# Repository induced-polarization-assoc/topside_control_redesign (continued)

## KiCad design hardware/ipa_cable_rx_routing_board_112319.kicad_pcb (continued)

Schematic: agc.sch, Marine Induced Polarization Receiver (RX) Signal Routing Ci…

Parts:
C901, C902, C911, C912, C921, C922, C931, C932: 10uF; CP_Elec_4x5.4
C903, C904, C907, C908, C925, C926, C929, C930: 0.1uF; C_0805_2012Metric
C905, C906, C927, C928: 10pF; C_0805_2012Metric
C909, C910, C923, C924: 0.33uF; C_0805_2012Metric
C913, C914, C919, C920: 2.2uF; C_0805_2012Metric
C915, C916, C917, C918: 0.022uF; C_0805_2012Metric
IC901, IC902, IC903, IC904: ADP3339AKCZ-1.5-R7; SOT-223-3_TabPin2
R901, R904, R929, R932: 1M; R_0805_2012Metric
R902, R903, R907, R908, R911, R912, R913, R914, R919, R920, R921, R922, R925, R926, R930, R931: 1K; R_0805_2012Metric
R905, R906, R927, R928: 100K; R_0805_2012Metric
R909, R910, R923, R924: 9.09K; R_0805_2012Metric
R915, R916, R917, R918: 10K; R_0805_2012Metric
RV901, RV902, RV903, RV904: 100K; Potentiometer_Vishay_TS53YJ_Vertical
U901, U904, U906, U909: AD8336ACPZ-R7; LFCSP-16-1EP_3x3mm_P0.5mm_EP1.6x1.6mm_ThermalVias
U902, U903, U907, U908: AD736ARZ; SOIC-8_3.9x4.9mm_P1.27mm
U905: AD8554ARZ-REEL7; SOIC-14_3.9x8.7mm_P1.27mm

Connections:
+5VA: C907.1, C908.1, C925.1, C926.1, IC901.3 (IN), IC902.3 (IN), IC903.3 (IN), IC904.3 (IN), U901.13 (VPOS), U902.7 (+VS), U903.7 (+VS), U904.13 (VPOS), U905.4 (V+), U906.13 (VPOS), U907.7 (+VS), U908.7 (+VS), U909.13 (VPOS); also elsewhere on the board
-5VA: C909.2, C910.2, C923.2, C924.2, U901.10 (VNEG), U902.4 (-VS), U903.4 (-VS), U904.10 (VNEG), U906.10 (VNEG), U907.4 (-VS), U908.4 (-VS), U909.10 (VNEG); also elsewhere on the board
/RA: R902.2; also elsewhere on the board
/RB: R930.2; also elsewhere on the board
/RC: R903.2; also elsewhere on the board
/RD: R931.2; also elsewhere on the board
/auto_gain_control/AGC_1_OUT: C901.2; also elsewhere on the board
/auto_gain_control/AGC_2_OUT: C931.2; also elsewhere on the board
/auto_gain_control/AGC_3_OUT: C902.2; also elsewhere on the board
/auto_gain_control/AGC_4_OUT: C932.2; also elsewhere on the board
/auto_gain_control/agc_1/AGC_A_FEEDBACK: C915.2, R915.1, U902.6 (OUTPUT), U905.6 (-INB)
/auto_gain_control/agc_1/AGC_A_GPOS: C913.1, C915.1, U901.11 (GPOS), U905.7 (OUTB)
/auto_gain_control/agc_1/AGC_A_TRIM: RV901.2, U905.5 (+INB)
/auto_gain_control/agc_1/AGC_B_FEEDBACK: C917.2, R917.1, U905.2 (-INA), U907.6 (OUTPUT)
/auto_gain_control/agc_1/AGC_B_GPOS: C917.1, C919.1, U905.1 (OUTA), U906.11 (GPOS)
/auto_gain_control/agc_1/AGC_B_TRIM: RV903.2, U905.3 (+INA)
/auto_gain_control/agc_1/AGC_C_FEEDBACK: C916.2, R916.1, U903.6 (OUTPUT), U905.9 (-INC)
/auto_gain_control/agc_1/AGC_C_GPOS: C914.1, C916.1, U904.11 (GPOS), U905.8 (OUTC)
/auto_gain_control/agc_1/AGC_C_TRIM: RV902.2, U905.10 (+INC)
/auto_gain_control/agc_1/AGC_D_FEEDBACK: C918.2, R918.1, U905.13 (-IND), U908.6 (OUTPUT)
/auto_gain_control/agc_1/AGC_D_GPOS: C918.1, C920.1, U905.14 (OUTD), U909.11 (GPOS)
/auto_gain_control/agc_1/AGC_D_TRIM: RV904.2, U905.12 (+IND)
/auto_gain_control/agc_1/GNEG: R911.1, R912.1, R913.2, R914.2, R919.2, R920.2, R921.1, R922.1, U901.12 (GNEG), U904.12 (GNEG), U906.12 (GNEG), U909.12 (GNEG)
GNDA: C907.2, C908.2, C911.2, C912.2, C921.2, C922.2, C925.2, C926.2, R901.1, R904.1, R913.1, R914.1, R919.1, R920.1, R929.1, R932.1, RV901.3, RV902.3, RV903.3, RV904.3, U901.2 (PWRA), U901.3 (VCOM), U901.4 (INPP), U901.17 (EPAD), U902.1 (CC), U902.8 (COM), U903.1 (CC), U903.8 (COM), U904.2 (PWRA), U904.3 (VCOM), U904.4 (INPP), U904.17 (EPAD), U905.11 (V-), U906.2 (PWRA), U906.3 (VCOM), U906.4 (INPP), U906.17 (EPAD), U907.1 (CC), U907.8 (COM), U908.1 (CC), U908.8 (COM), U909.2 (PWRA), U909.3 (VCOM), U909.4 (INPP), U909.17 (EPAD); also elsewhere on the board
unnamed: C901.1, C903.1, R905.2
unnamed: C902.1, C904.1, R906.2
unnamed: C903.2, R904.2, U902.2 (VIN)
unnamed: C904.2, R901.2, U903.2 (VIN)
unnamed: C905.1, R907.1, U901.8 (PRAO), U901.9 (VGAI)
unnamed: C905.2, R902.1, R907.2, U901.5 (INPN)
unnamed: C906.1, R908.1, U904.8 (PRAO), U904.9 (VGAI)
unnamed: C906.2, R903.1, R908.2, U904.5 (INPN)
unnamed: C909.1, U902.5 (CAV)
unnamed: C910.1, U903.5 (CAV)
unnamed: C911.1, IC901.1 (GND), IC901.2 (OUT), R909.2, R911.2
unnamed: C912.1, IC902.1 (GND), IC902.2 (OUT), R910.2, R912.2
unnamed: C913.2, R915.2
unnamed: C914.2, R916.2
unnamed: C919.2, R917.2
unnamed: C920.2, R918.2
unnamed: C921.1, IC903.1 (GND), IC903.2 (OUT), R921.2, R923.2
unnamed: C922.1, IC904.1 (GND), IC904.2 (OUT), R922.2, R924.2
unnamed: C923.1, U907.5 (CAV)
unnamed: C924.1, U908.5 (CAV)
unnamed: C927.1, R925.1, U906.8 (PRAO), U906.9 (VGAI)
unnamed: C927.2, R925.2, R930.1, U906.5 (INPN)
unnamed: C928.1, R926.1, U909.8 (PRAO), U909.9 (VGAI)
unnamed: C928.2, R926.2, R931.1, U909.5 (INPN)
unnamed: C929.1, C931.1, R927.2
unnamed: C929.2, R929.2, U907.2 (VIN)
unnamed: C930.1, C932.1, R928.2
unnamed: C930.2, R932.2, U908.2 (VIN)
unnamed: R905.1, U901.1 (VOUT)
unnamed: R906.1, U904.1 (VOUT)
unnamed: R909.1, RV901.1
unnamed: R910.1, RV902.1
unnamed: R923.1, RV903.1
unnamed: R924.1, RV904.1
unnamed: R927.1, U906.1 (VOUT)
unnamed: R928.1, U909.1 (VOUT)

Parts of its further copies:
C1001, C1002, C1011, C1012, C1021, C1022, C1031, C1032: 10uF; CP_Elec_4x5.4
C1003, C1004, C1007, C1008, C1025, C1026, C1029, C1030: 0.1uF; C_0805_2012Metric
C1005, C1006, C1027, C1028: 10pF; C_0805_2012Metric
C1009, C1010, C1023, C1024: 0.33uF; C_0805_2012Metric
C1013, C1014, C1019, C1020: 2.2uF; C_0805_2012Metric
C1015, C1016, C1017, C1018: 0.022uF; C_0805_2012Metric
IC1001, IC1002, IC1003, IC1004: ADP3339AKCZ-1.5-R7; SOT-223-3_TabPin2
R1001, R1004, R1029, R1032: 1M; R_0805_2012Metric
R1002, R1003, R1007, R1008, R1011, R1012, R1013, R1014, R1019, R1020, R1021, R1022, R1025, R1026, R1030, R1031: 1K; R_0805_2012Metric
R1005, R1006, R1027, R1028: 100K; R_0805_2012Metric
R1009, R1010, R1023, R1024: 9.09K; R_0805_2012Metric
R1015, R1016, R1017, R1018: 10K; R_0805_2012Metric
RV1001, RV1002, RV1003, RV1004: 100K; Potentiometer_Vishay_TS53YJ_Vertical
U1001, U1004, U1006, U1009: AD8336ACPZ-R7; LFCSP-16-1EP_3x3mm_P0.5mm_EP1.6x1.6mm_ThermalVias
U1002, U1003, U1007, U1008: AD736ARZ; SOIC-8_3.9x4.9mm_P1.27mm
U1005: AD8554ARZ-REEL7; SOIC-14_3.9x8.7mm_P1.27mm

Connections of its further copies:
+5VA: C1007.1, C1008.1, C1025.1, C1026.1, IC1001.3 (IN), IC1002.3 (IN), IC1003.3 (IN), IC1004.3 (IN), U1001.13 (VPOS), U1002.7 (+VS), U1003.7 (+VS), U1004.13 (VPOS), U1005.4 (V+), U1006.13 (VPOS), U1007.7 (+VS), U1008.7 (+VS), U1009.13 (VPOS); also elsewhere on the board
-5VA: C1009.2, C1010.2, C1023.2, C1024.2, U1001.10 (VNEG), U1002.4 (-VS), U1003.4 (-VS), U1004.10 (VNEG), U1006.10 (VNEG), U1007.4 (-VS), U1008.4 (-VS), U1009.10 (VNEG); also elsewhere on the board
/RE: R1002.2; also elsewhere on the board
/RF: R1030.2; also elsewhere on the board
/RG: R1003.2; also elsewhere on the board
/RH: R1031.2; also elsewhere on the board
/auto_gain_control/AGC_5_OUT: C1001.2; also elsewhere on the board
/auto_gain_control/AGC_6_OUT: C1031.2; also elsewhere on the board
/auto_gain_control/AGC_7_OUT: C1002.2; also elsewhere on the board
/auto_gain_control/AGC_8_OUT: C1032.2; also elsewhere on the board
/auto_gain_control/agc_2/AGC_A_FEEDBACK: C1015.2, R1015.1, U1002.6 (OUTPUT), U1005.6 (-INB)
/auto_gain_control/agc_2/AGC_A_GPOS: C1013.1, C1015.1, U1001.11 (GPOS), U1005.7 (OUTB)
/auto_gain_control/agc_2/AGC_A_TRIM: RV1001.2, U1005.5 (+INB)
/auto_gain_control/agc_2/AGC_B_FEEDBACK: C1017.2, R1017.1, U1005.2 (-INA), U1007.6 (OUTPUT)
/auto_gain_control/agc_2/AGC_B_GPOS: C1017.1, C1019.1, U1005.1 (OUTA), U1006.11 (GPOS)
/auto_gain_control/agc_2/AGC_B_TRIM: RV1003.2, U1005.3 (+INA)
/auto_gain_control/agc_2/AGC_C_FEEDBACK: C1016.2, R1016.1, U1003.6 (OUTPUT), U1005.9 (-INC)
/auto_gain_control/agc_2/AGC_C_GPOS: C1014.1, C1016.1, U1004.11 (GPOS), U1005.8 (OUTC)
/auto_gain_control/agc_2/AGC_C_TRIM: RV1002.2, U1005.10 (+INC)
/auto_gain_control/agc_2/AGC_D_FEEDBACK: C1018.2, R1018.1, U1005.13 (-IND), U1008.6 (OUTPUT)
/auto_gain_control/agc_2/AGC_D_GPOS: C1018.1, C1020.1, U1005.14 (OUTD), U1009.11 (GPOS)
/auto_gain_control/agc_2/AGC_D_TRIM: RV1004.2, U1005.12 (+IND)
/auto_gain_control/agc_2/GNEG: R1011.1, R1012.1, R1013.2, R1014.2, R1019.2, R1020.2, R1021.1, R1022.1, U1001.12 (GNEG), U1004.12 (GNEG), U1006.12 (GNEG), U1009.12 (GNEG)
GNDA: C1007.2, C1008.2, C1011.2, C1012.2, C1021.2, C1022.2, C1025.2, C1026.2, R1001.1, R1004.1, R1013.1, R1014.1, R1019.1, R1020.1, R1029.1, R1032.1, RV1001.3, RV1002.3, RV1003.3, RV1004.3, U1001.2 (PWRA), U1001.3 (VCOM), U1001.4 (INPP), U1001.17 (EPAD), U1002.1 (CC), U1002.8 (COM), U1003.1 (CC), U1003.8 (COM), U1004.2 (PWRA), U1004.3 (VCOM), U1004.4 (INPP), U1004.17 (EPAD), U1005.11 (V-), U1006.2 (PWRA), U1006.3 (VCOM), U1006.4 (INPP), U1006.17 (EPAD), U1007.1 (CC), U1007.8 (COM), U1008.1 (CC), U1008.8 (COM), U1009.2 (PWRA), U1009.3 (VCOM), U1009.4 (INPP), U1009.17 (EPAD); also elsewhere on the board
unnamed: C1001.1, C1003.1, R1005.2
unnamed: C1002.1, C1004.1, R1006.2
unnamed: C1003.2, R1004.2, U1002.2 (VIN)
unnamed: C1004.2, R1001.2, U1003.2 (VIN)
unnamed: C1005.1, R1007.1, U1001.8 (PRAO), U1001.9 (VGAI)
unnamed: C1005.2, R1002.1, R1007.2, U1001.5 (INPN)
unnamed: C1006.1, R1008.1, U1004.8 (PRAO), U1004.9 (VGAI)
unnamed: C1006.2, R1003.1, R1008.2, U1004.5 (INPN)
unnamed: C1009.1, U1002.5 (CAV)
unnamed: C1010.1, U1003.5 (CAV)
unnamed: C1011.1, IC1001.1 (GND), IC1001.2 (OUT), R1009.2, R1011.2
unnamed: C1012.1, IC1002.1 (GND), IC1002.2 (OUT), R1010.2, R1012.2
unnamed: C1013.2, R1015.2
unnamed: C1014.2, R1016.2
unnamed: C1019.2, R1017.2
unnamed: C1020.2, R1018.2
unnamed: C1021.1, IC1003.1 (GND), IC1003.2 (OUT), R1021.2, R1023.2
unnamed: C1022.1, IC1004.1 (GND), IC1004.2 (OUT), R1022.2, R1024.2
unnamed: C1023.1, U1007.5 (CAV)
unnamed: C1024.1, U1008.5 (CAV)
unnamed: C1027.1, R1025.1, U1006.8 (PRAO), U1006.9 (VGAI)
unnamed: C1027.2, R1025.2, R1030.1, U1006.5 (INPN)
unnamed: C1028.1, R1026.1, U1009.8 (PRAO), U1009.9 (VGAI)
unnamed: C1028.2, R1026.2, R1031.1, U1009.5 (INPN)
unnamed: C1029.1, C1031.1, R1027.2
unnamed: C1029.2, R1029.2, U1007.2 (VIN)
unnamed: C1030.1, C1032.1, R1028.2
unnamed: C1030.2, R1032.2, U1008.2 (VIN)
unnamed: R1005.1, U1001.1 (VOUT)
unnamed: R1006.1, U1004.1 (VOUT)
unnamed: R1009.1, RV1001.1
unnamed: R1010.1, RV1002.1
unnamed: R1023.1, RV1003.1
unnamed: R1024.1, RV1004.1
unnamed: R1027.1, U1006.1 (VOUT)
unnamed: R1028.1, U1009.1 (VOUT)

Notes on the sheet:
AGC GAIN CONTROL OP AMP (QUAD UNIT)

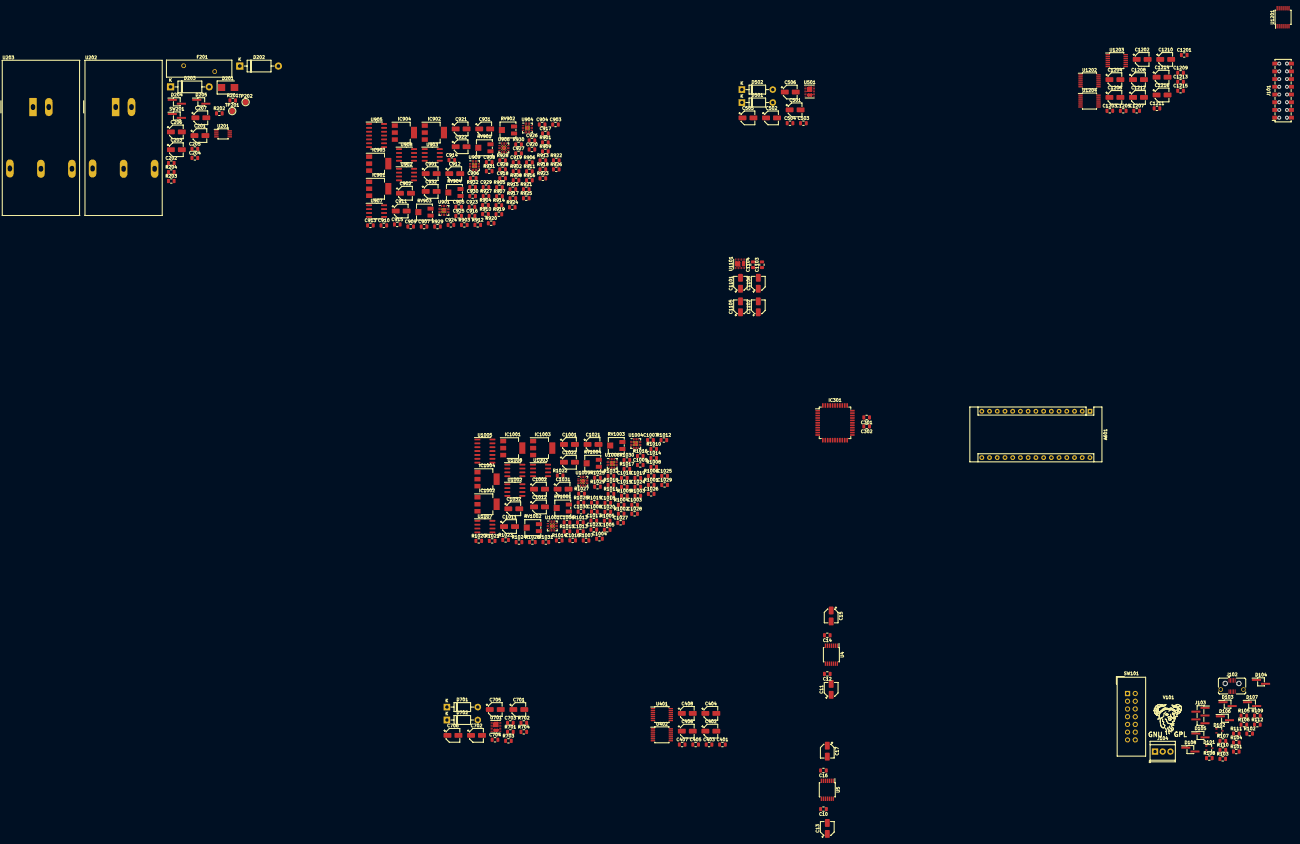
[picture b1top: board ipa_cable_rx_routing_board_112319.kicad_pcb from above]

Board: 4 copper layers, 284 parts (0 on the bottom side), 215 nets.

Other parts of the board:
C10, C12, C14, C16: 0.1uF; C_0805_2012Metric
C11, C13, C15, C17: 10uF; CP_Elec_4x5.4
U4, U5: ADA4807-4; TSSOP-14_4.4x5mm_P0.65mm

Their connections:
+12VA: C14.1, C15.2, C16.1, C17.2, U4.4, U5.4; also elsewhere on the board
-12VA: C10.1, C11.2, C12.1, C13.2, U4.11, U5.11; also elsewhere on the board
/auto_gain_control/AGC_1_OUT: U4.3; also elsewhere on the board
/auto_gain_control/AGC_2_OUT: U4.5; also elsewhere on the board
/auto_gain_control/AGC_3_OUT: U4.10; also elsewhere on the board
/auto_gain_control/AGC_4_OUT: U4.12; also elsewhere on the board
/auto_gain_control/AGC_5_OUT: U5.3; also elsewhere on the board
/auto_gain_control/AGC_6_OUT: U5.5; also elsewhere on the board
/auto_gain_control/AGC_7_OUT: U5.10; also elsewhere on the board
/auto_gain_control/AGC_8_OUT: U5.12; also elsewhere on the board
/crosspoint_switch_array/RA: U4.1, U4.2; also elsewhere on the board
/crosspoint_switch_array/RB: U4.6, U4.7; also elsewhere on the board
/crosspoint_switch_array/RC: U4.8, U4.9; also elsewhere on the board
/crosspoint_switch_array/RD: U4.13, U4.14; also elsewhere on the board
/crosspoint_switch_array/RE: U5.1, U5.2; also elsewhere on the board
/crosspoint_switch_array/RF: U5.6, U5.7; also elsewhere on the board
/crosspoint_switch_array/RG: U5.8, U5.9; also elsewhere on the board
/crosspoint_switch_array/RH: U5.13, U5.14; also elsewhere on the board
GNDA: C10.2, C11.1, C12.2, C13.1, C14.2, C15.1, C16.2, C17.1; also elsewhere on the board

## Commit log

2020-03-25 Create .gitattributes
    Implementing file management filters for git clean and git smudge commands.
2020-03-25 Added a configuration script for the repo for smoother integration with KiCAD.
2020-03-25 Added permission to execute the script...
2020-03-25 Typo fixed in shebang...
2020-03-25 Added some indicator echoes to the script.
2020-03-25 Added a check for Mac users to ensure *.DS_Store is omitted.
2020-03-25 Cleaned up the dotfiles a little.
2020-03-25 Added design drawings from KiCAD into the repo.
2020-03-25 Backlink to CADLAB.io has been added.
